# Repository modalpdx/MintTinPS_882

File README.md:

#MintTinPS_882

A simple power supply board for "standard" mint tins. Examples: Altoids,
Penguin Mints, Mintz. The board is sized/shaped to fit in the tin while
still allowing enough room for up to three AA batteries in an open holder
and a mini-toggle to switch the power supply on/off.

[*Note: There are current limitations with this design that drove me to
design a more powerful board: the MintTinPS_604 which uses a MAX604
regulator instead of a MAX882 regulator. I recommend you skip this board
and go with that one instead. I'll leave these files here because why
not...*]

This version of the mint tin power supply uses a [**Maxim MAX882 linear voltage regulator**](http://www.maximintegrated.com/en/products/power/linear-regulators/MAX882.html "MAX882 Info"), which gives us the following output voltage options:

* Default voltage: 3.3V
* Adjustable voltage: 1.25V to 11V

The adjustable voltage is activated by setting a jumper (ADJV). If the
jumper is open, you get 3.3V.

##Parts
* Maxim MAX882 voltage regulator (8 pin DIP)
* 8 pin DIP socket (optional, but smart)
* 0.1uF capacitor (ceramic, C2 on the board)
* 2.2uF capacitor (polarized, C1 on the board)
* 10k Bourns trimmer potentiometer (3306)
* 2-pin male header (2.54mm/0.1") & jumper

Optional for power connection:
* 2 x 2 male header (2.54mm/0.1"), right-angled 
* Two 1 x 2 female headers (2.54mm/0.1") for power wires

Other:
* "Standard" size mint tin (ex: large Altoids/Mintz/Penguin Mints tin)
* .125" spacers (I'm guessing adhesive, nylon) if spacers are your thing
* Something else to fully insulate the bottom of the board

##Setting the adjustable voltage

The level of the adjustable voltage is set with a trimmer potentiometer on
the board. Connect the output power wires (POW|out) to a multimeter, set
the multimeter to read DC voltage, then turn the potentiometer until you
have your desired voltage. You are limited by the voltage that is put out
by your batteries (there is no boost circuitry in this power supply).
Also, make sure you are not powering any components with the power supply
when you adjust the voltage.

##Implementation

I intentionally left the power connections (POW|in/out) generic so you can
connect whatever battery you wish to connect in the manner in which you'd
like to connect it, *as long as you keep in mind that your power source
has to be between 2.7V and 11.5V*. 

Until 5V goes out of fashion, I'm using a 9V battery with this. No
combination of inline AA or AAA batteries will get high enough voltage to
provide >5V and still fit in a mint tin.  When 5V goes away, three AA
batteries should work.

The use of a jumper for switching voltages was intentional. Anything that
can switch from a lower to a higher voltage should involve some user
experience "friction." If the voltage switch is exposed on the outside of
the tin, it could be accidentally bumped. Depending on what voltage was
switched to, this could result in fried components. Keeping the voltage
switching experience inside the tin makes more sense.

There are no LEDs for power status, either. Feel free to add them if you
like. I wanted all power to go to the circuit I'm designing, not
blinkenlights.

##Limitations

* Input voltage range: 2.7V to 11.5V
* Output voltage range: 1.25V to 11V (input voltage limits upper value)
* Non-adjustable voltage: 3.3V
* No voltage boost capabilities
* Maximum current: 200mA
* Linear regulators are not the most efficient

This is a perfectly capable power supply for breadboarding. If you need a
power supply for something else, this isn't it. 

##Motivation

I wanted to have a small breadboard/power supply combo that would be
compact, self-contained, and offer two voltages. There are projects on the
Internet that do this already but they either skimp on the voltages (only
offer one, typically 5V) or they default to 5V and 9V (I have never needed
9V on a breadboard before, and I probably never will). 

I also wanted to future-proof the power supply.
Right now the common component voltages seem to be 3.3V and 5V, but 5V
components are becoming less common. It makes more sense to have a power
supply that offers 3.3V plus one adjustable voltage, so when 5V goes away,
I'll still have 3.3V and one other up-and-coming voltage (looks like 2.5V
may be the next one).

##Miscellaneous Notes

If you want the power supply to default to 5V instead of 3.3V, the Maxim
MAX883 should be a drop-in replacement for the MAX882. This chip would
give you everything the MAX882 offers but the non-adjustable voltage would
be 5V. The adjustable voltage is handled identically to the MAX882.

The first run of PCBs from DirtyPCBs has been tested and they work fine.
With the jumper out I get 3.3V and with the jumper in I get my adjustable,
dialed-in voltage.

##VERSIONS

0.1 - Initial version.

0.2 - Fixed arrangement of power pins, mount holes now .125", fixed silk
on bottom, fixed C1 on schematic.

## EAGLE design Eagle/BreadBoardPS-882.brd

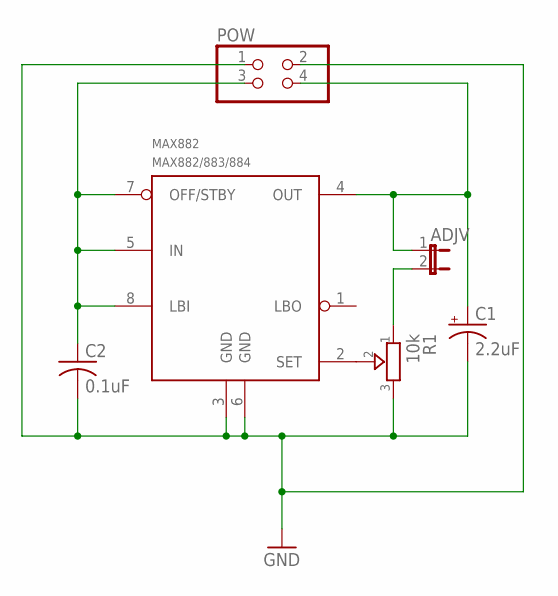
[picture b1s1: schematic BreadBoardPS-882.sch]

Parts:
ADJV: JP1E; JP1
C1: 2.2uF; E2,5-5
C2: 0.1uF; C025-024X044
MAX882: MAX882/883/884; DIL08
POW: PINHD-2X22X02/90NOSILK; 2X02/90
R1: 10k; TRIMMER_3306F

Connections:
GND: C1.-, C2.2, MAX882.3 (GND), MAX882.6 (GND), POW.1, POW.2, R1.3
unnamed: C2.1, MAX882.5 (IN), MAX882.7 (OFF/STBY), MAX882.8 (LBI), POW.3
unnamed: ADJV.2, R1.1
unnamed: ADJV.1, C1.+, MAX882.4 (OUT), POW.4
unnamed: MAX882.2 (SET), R1.2

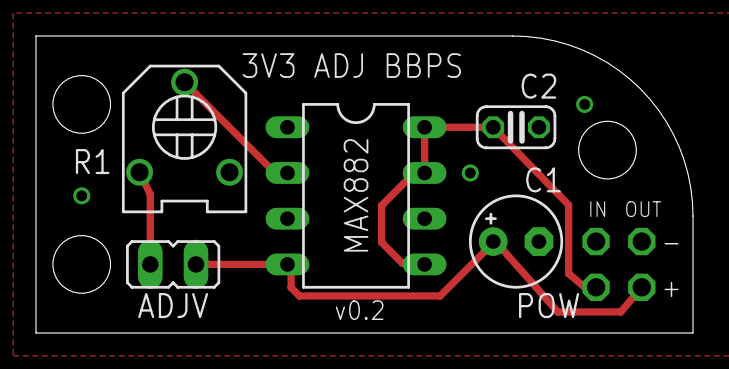
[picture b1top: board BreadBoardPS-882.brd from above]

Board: 2 copper layers, 36.5 x 16.5 mm, 6 parts (0 on the bottom side), 5 nets.

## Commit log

2014-09-22 Initial checkin with DirtyPCBs gerbers.
2014-09-22 Damn DS_Store files. Gotta add that to the ignore file.
2014-09-22 Minor markdown styling issue.
2014-09-22 Added parts list.
2014-09-22 Typo.
2014-10-30 Added note about PCBs not being tested yet.
2014-11-01 Updated README.
2014-11-03 Updated the notes to reflect a successful test run.
2014-11-03 Fixed an awkward note. I should be done now.
2014-11-03 Trying out a markdown link. HTML is easier.
2014-12-09 Housecleaning.
2014-12-09 Updated README to point people to the MAX604 version of the board
2014-12-10 An image of the finished product.
2014-12-10 Not planning to fix the silk on the back of the board. Not. No way Jose.
2014-12-20 Board 0.2. Fixed mount holes, power in/out, silk on bottom. New gerbers.
2014-12-20 Fixed C1 on schematic (and updated the board), README notes.
2014-12-20 Fixed the schematic again because I didn't fix it correctly the first time. My bad.
2014-12-20 Updated schematic PDF.
